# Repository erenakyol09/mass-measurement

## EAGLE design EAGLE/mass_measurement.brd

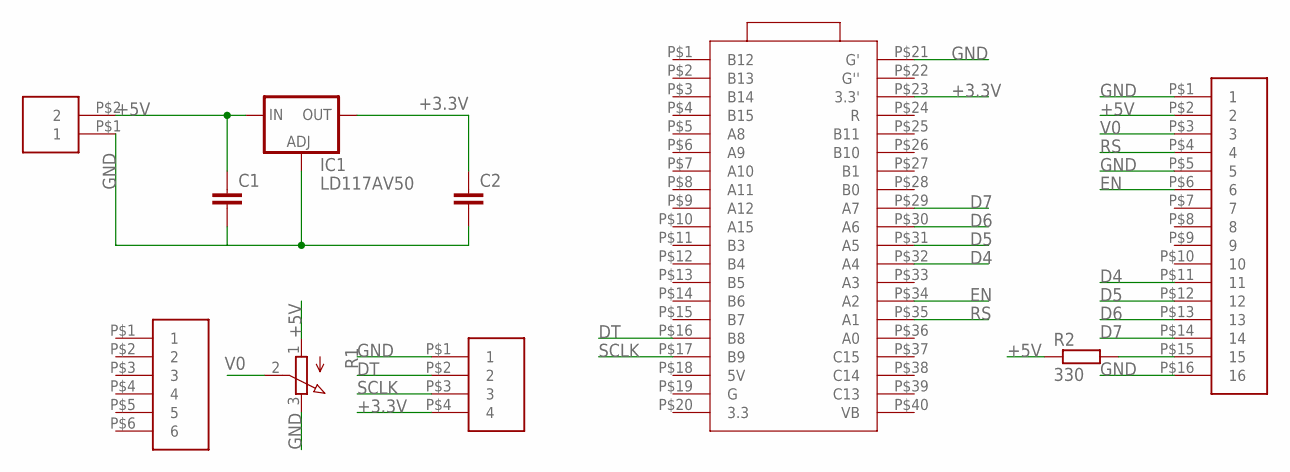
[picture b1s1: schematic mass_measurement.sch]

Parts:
C1, C2: C-EU025-030X050; C025-030X050
IC1: LD117AV50; TO220L1
R1: 3RP/1610N
R2: 330; 0617/17
U$1: HEADER_2; HEADER_2_FOOT
U$2: HEADER_16; HEADER_16_FOOT
U$3: BLUE_PILL_EA; BLUE_PILL_FOOT
U$4: HEADER_4; HEADER_4_FOOT
U$5: HEADER_6; HEADER_6_FOOT

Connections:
+3.3V: C2.1, IC1.2 (OUT), U$3.P$23 (3.3'), U$4.P$4 (4)
+5V: C1.1, IC1.3 (IN), R1.1 (A), R2.1, U$1.P$2 (2), U$2.P$2 (2)
D4: U$2.P$11 (11), U$3.P$32 (A4)
D5: U$2.P$12 (12), U$3.P$31 (A5)
D6: U$2.P$13 (13), U$3.P$30 (A6)
D7: U$2.P$14 (14), U$3.P$29 (A7)
DT: U$3.P$16 (B8), U$4.P$2 (2)
EN: U$2.P$6 (6), U$3.P$34 (A2)
GND: C1.2, C2.2, IC1.1 (ADJ), R1.3 (E), U$1.P$1 (1), U$2.P$1 (1), U$2.P$5 (5), U$2.P$16 (16), U$3.P$21 (G'), U$4.P$1 (1)
unnamed: R2.2, U$2.P$15 (15)
RS: U$2.P$4 (4), U$3.P$35 (A1)
SCLK: U$3.P$17 (B9), U$4.P$3 (3)
V0: R1.2 (S), U$2.P$3 (3)

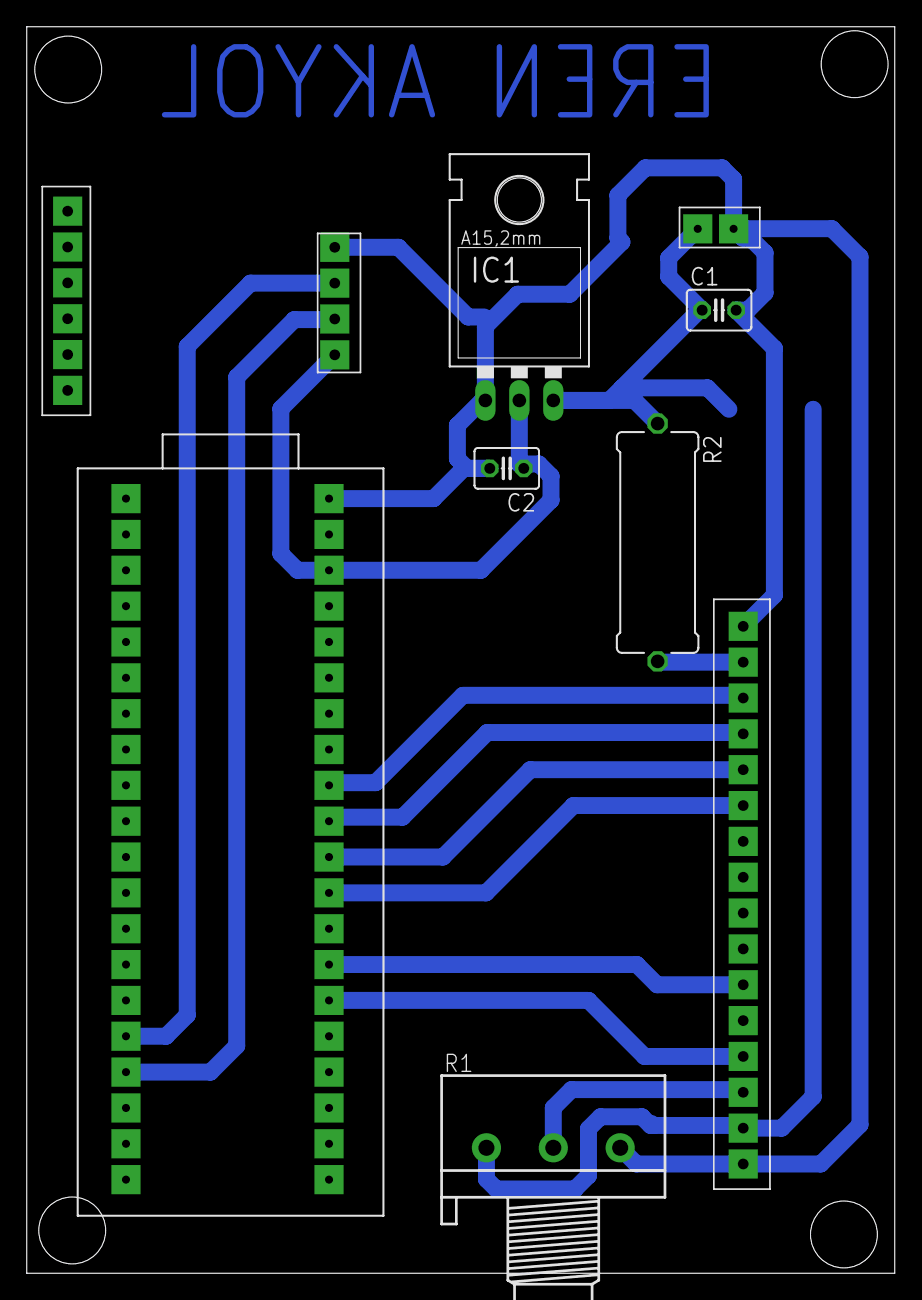
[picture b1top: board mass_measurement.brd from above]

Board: 2 copper layers, 64.9 x 93.2 mm, 10 parts (0 on the bottom side), 13 nets.

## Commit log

2020-07-20 mass reading 1
2021-01-02 Update hx711.h
    (HX711_Average_Value) in c lib named HX711_Average_Value but it called on .h header (HX711_AverageValue)
    please edit it
